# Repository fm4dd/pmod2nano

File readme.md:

## PMOD2NANO

### Description

This module is a PMOD adapter for Intels DE0-Nano-SoC boards. DE0-Nano-SoC boards, equipped with Cyclone V FPGA, provide generic IO access through two proprietary 40-pin header rows with 36 IOs (72 IO total). The PMOD2NANO adapter converts 16 board IO's, together with the power lines, into two dual-row PMOD sockets. The adapter can be used on both GPIO rows for a total of four PMOD connectors.

http://fpga.fm4dd.com/

### Schematic

### PCB Gerber

[PMOD2NANO GPIO-0 Silkscreen Gerber V1.0](20200112-pmod2nano-gpio0-gerber-v10.zip)

[PMOD2NANO GPIO-1 Silkscreen Gerber V1.0](20200128-pmod2nano-gpio1-gerber-v10.zip)

### Pin Assignments

#### DE0-Nano-SoC

PMOD1|  Label | GPIO0A | GPIO1A | PMOD2|  Label | GPIO0B | GPIO1B
-----|--------|--------|--------|------|--------|--------|--------
1    |  IO1   | PIN_W12|PIN_AA15| 1    |  IO9   | PIN_AF4| PIN_AH23
2    |  IO2   | PIN_Y8 |PIN_AG26| 2    |  IO10  | PIN_AF5| PIN_AE19
3    |  IO3   | PIN_W8 |PIN_AF23| 3    |  IO11  | PIN_T13| PIN_AD19
4    |  IO4   | PIN_Y5 |PIN_AF21| 4    |  IO12  | PIN_AE7| PIN_AE24
7    |  IO5   | PIN_AF8|PIN_AH27| 7    |  IO13  | PIN_AG6| PIN_AG23
8    |  IO6   | PIN_AB4|PIN_AH24| 8    |  IO14  | PIN_AE4| PIN_AF18
9    |  IO7   | PIN_Y4 |PIN_AE22| 9    |  IO15  | PIN_T11| PIN_AE20
10   |  IO8   | PIN_U11|PIN_AG20| 10   |  IO16  | PIN_AF6| PIN_AD20

### Examples

7seg4 PMOD, connected through the PMOD2NANO adapter

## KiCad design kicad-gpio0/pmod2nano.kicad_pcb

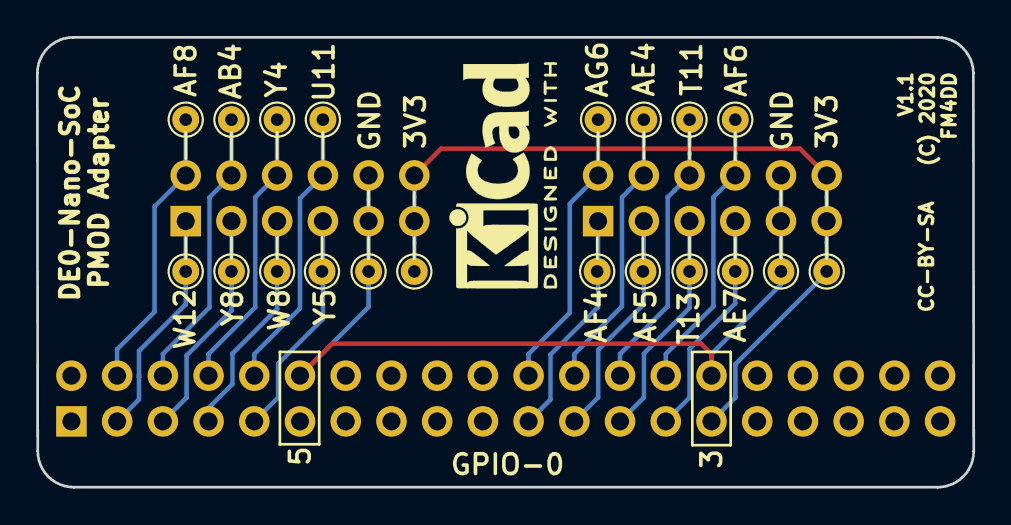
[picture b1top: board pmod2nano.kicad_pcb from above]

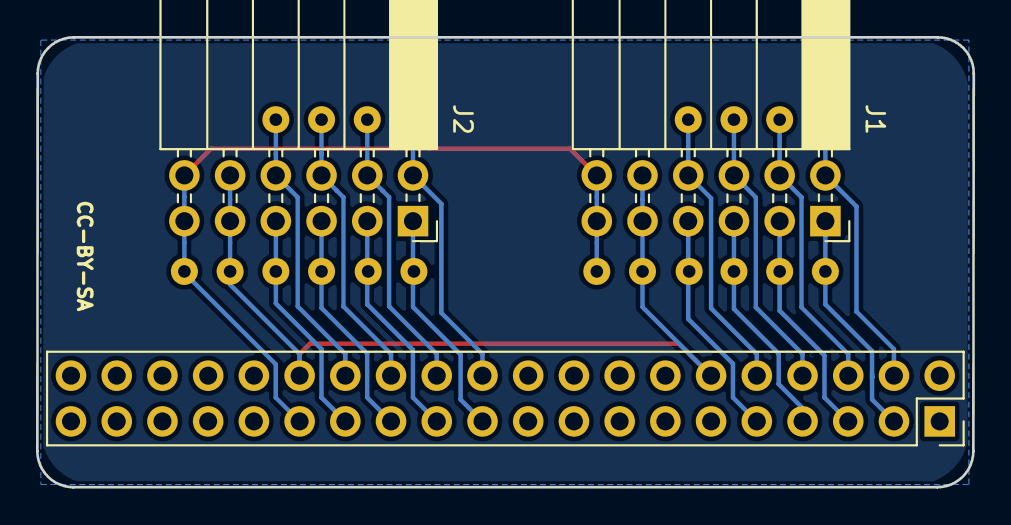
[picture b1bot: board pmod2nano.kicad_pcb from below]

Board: 2 copper layers, 52.0 x 25.0 mm, 3 parts (3 on the bottom side), 18 nets.

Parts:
J1, J2: PMOD; PinSocket_2x06_P2.54mm_Horizontal
J3: Conn_02x20_Odd_Even; PinSocket_2x20_P2.54mm_Vertical

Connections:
+3V3: J1.11, J1.12, J2.11, J2.12, J3.29
/PIN_AB4: J1.4, J3.6
/PIN_AE4: J2.4, J3.24
/PIN_AE7: J2.7, J3.27
/PIN_AF4: J2.1, J3.21
/PIN_AF5: J2.3, J3.23
/PIN_AF6: J2.8, J3.28
/PIN_AF8: J1.2, J3.4
/PIN_AG6: J2.2, J3.22
/PIN_T11: J2.6, J3.26
/PIN_T13: J2.5, J3.25
/PIN_U11: J1.8, J3.10
/PIN_W8: J1.5, J3.7
/PIN_W12: J1.1, J3.3
/PIN_Y4: J1.6, J3.8
/PIN_Y5: J1.7, J3.9
/PIN_Y8: J1.3, J3.5
GND: J1.9, J1.10, J2.9, J2.10, J3.12, J3.30

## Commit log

2020-03-20 add fpga url
2020-04-23 Add GPIO-1 silkscreen version
2021-08-25 testpin update gpio0

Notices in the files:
kicad-gpio0/pmod2nano.kicad_pcb:
License: CC-BY-SA 4.0
CC-BY-SA
(C) 2020
